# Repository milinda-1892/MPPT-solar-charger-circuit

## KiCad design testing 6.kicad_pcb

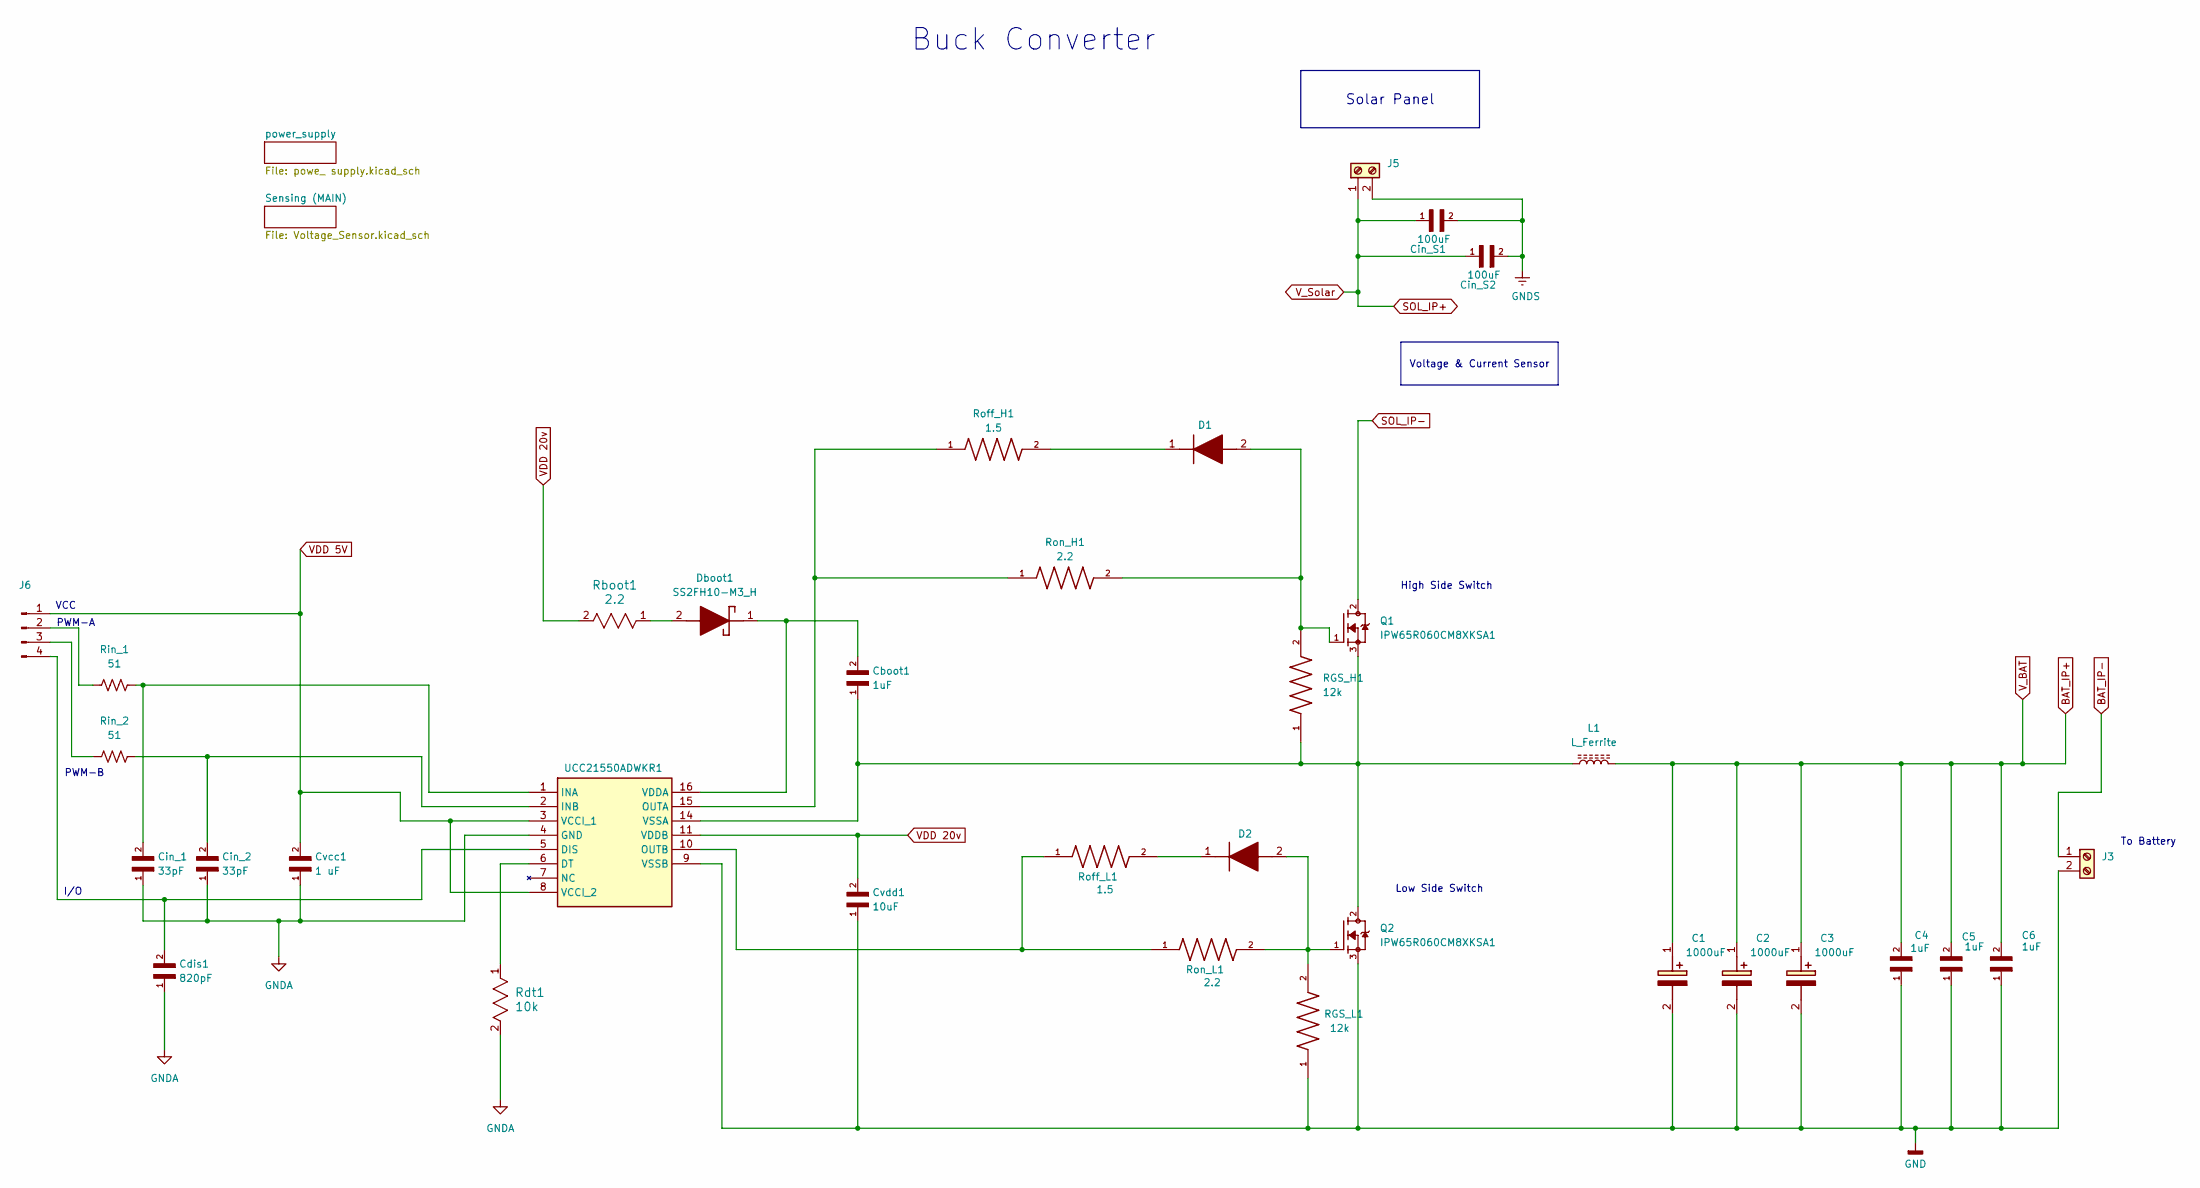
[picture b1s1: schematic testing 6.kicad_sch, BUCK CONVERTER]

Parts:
C1, C2, C3: 1000uF; CP_Radial_D16.0mm_P7.50mm; Mouser Part Number 594-MAL214699814E3
C4, C5, C6: 1uF; C_1210_3225Metric_Pad1.33x2.70mm_HandSolder
Cboot1: 1uF; C_1210_3225Metric_Pad1.33x2.70mm_HandSolder
Cdis1: 820pF; C_1206_3216Metric_Pad1.33x1.80mm_HandSolder
Cin_1, Cin_2: 33pF; C_0805_2012Metric_Pad1.18x1.45mm_HandSolder
Cin_S1, Cin_S2: 100uF; CP_Radial_D16.0mm_P7.50mm
Cvcc1: 1 uF; C_1210_3225Metric_Pad1.33x2.70mm_HandSolder
Cvdd1: 10uF; C_1210_3225Metric_Pad1.33x2.70mm_HandSolder
D1, D2: BYG20J-E3_TR; DIOM5127X229N; Mouser Part Number 625-BYG20J-E3
Dboot1: SS2FH10-M3_H; SODFL3718X108N; Mouser Part Number 78-SS2FH10-M3/H
J3, J5: Screw_Terminal_01x02; TerminalBlock_Phoenix_MPT-0,5-2-2.54_1x02_P2.54mm_Horizontal
J6: Conn_01x04_Pin; PinHeader_1x04_P2.00mm_Vertical
L1: L_Ferrite; L_Toroid_Vertical_L46.0mm_W19.1mm_P21.80mm_Bourns_5700
Q1, Q2: IPW65R060CM8XKSA1; TO544P521X1592X2557-3P; PARTREV 2.5
RGS_H1: 12k; R_1206_3216Metric_Pad1.30x1.75mm_HandSolder; PARTREV 3/1/2020
RGS_L1: 12k; R_1206_3216Metric_Pad1.30x1.75mm_HandSolder; PARTREV 3/1/2020
Rboot1: 2.2; R_0805_2012Metric_Pad1.20x1.40mm_HandSolder
Rdt1: 10k; R_0805_2012Metric_Pad1.20x1.40mm_HandSolder
Rin_1, Rin_2: 51; R_0805_2012Metric_Pad1.20x1.40mm_HandSolder
Roff_H1: 1.5; R_0805_2012Metric_Pad1.20x1.40mm_HandSolder
Roff_L1: 1.5; R_0805_2012Metric_Pad1.20x1.40mm_HandSolder
Ron_H1: 2.2; R_0805_2012Metric_Pad1.20x1.40mm_HandSolder
Ron_L1: 2.2; R_0805_2012Metric_Pad1.20x1.40mm_HandSolder
UCC21550ADWKR1: UCC21550ADWKR; UCC21550CDWKR; Mouser Part Number 595-UCC21550ADWKR

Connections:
BAT_IP+: C1.1 (+), C2.1 (+), C3.1 (+), C4.2, C5.2, C6.2, L1.2; also elsewhere on the board
BAT_IP-: J3.1; also elsewhere on the board
GND: C1.2 (-), C2.2 (-), C3.2 (-), C4.1, C5.1, C6.1, Cvdd1.1, J3.2, Q2.3, RGS_L1.1, UCC21550ADWKR1.9 (VSSB); also elsewhere on the board
GNDA: Cdis1.1, Cin_1.1, Cin_2.1, Cvcc1.1, Rdt1.2, UCC21550ADWKR1.4 (GND); also elsewhere on the board
GNDS: Cin_S1.2, Cin_S2.2, J5.2; also elsewhere on the board
unnamed: D1.2 (A), Q1.1, RGS_H1.2, Ron_H1.2
unnamed: D1.1 (K), Roff_H1.2
unnamed: D2.2 (A), Q2.1, RGS_L1.2, Ron_L1.2
unnamed: D2.1 (K), Roff_L1.2
unnamed: Dboot1.2 (A), Rboot1.1
unnamed: Cboot1.2, Dboot1.1 (K), UCC21550ADWKR1.16 (VDDA)
unnamed: J6.2, Rin_1.1
unnamed: J6.3, Rin_2.1
unnamed: Cdis1.2, J6.4, UCC21550ADWKR1.5 (DIS)
unnamed: Rdt1.1, UCC21550ADWKR1.6 (DT)
unnamed: Cin_1.2, Rin_1.2, UCC21550ADWKR1.1 (INA)
unnamed: Cin_2.2, Rin_2.2, UCC21550ADWKR1.2 (INB)
unnamed: Roff_H1.1, Ron_H1.1, UCC21550ADWKR1.15 (OUTA)
unnamed: Roff_L1.1, Ron_L1.1, UCC21550ADWKR1.10 (OUTB)
unnamed: Cboot1.1, L1.1, Q1.3, Q2.2, RGS_H1.1, UCC21550ADWKR1.14 (VSSA)
SOL_IP+: Cin_S1.1, Cin_S2.1, J5.1; also elsewhere on the board
SOL_IP-: Q1.2; also elsewhere on the board
VDD 5V: Cvcc1.2, J6.1, UCC21550ADWKR1.3 (VCCI_1), UCC21550ADWKR1.8 (VCCI_2); also elsewhere on the board
VDD 20v: Cvdd1.2, Rboot1.2, UCC21550ADWKR1.11 (VDDB); also elsewhere on the board

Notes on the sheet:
I/O
PWM-B
Low Side Switch
PWM-A
Buck Converter
High Side Switch
To Battery
VCC
Solar Panel
Voltage & Current Sensor

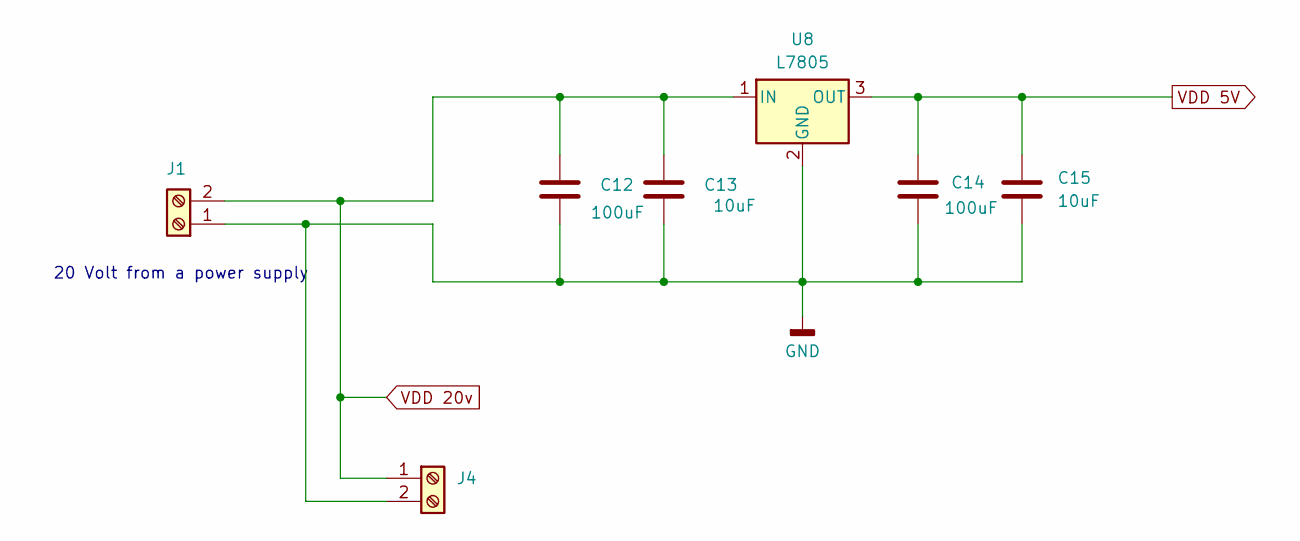
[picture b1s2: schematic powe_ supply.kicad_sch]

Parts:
C12, C14: 100uF; C_1206_3216Metric_Pad1.33x1.80mm_HandSolder
C13, C15: 10uF; C_1206_3216Metric_Pad1.33x1.80mm_HandSolder
J1, J4: Screw_Terminal_01x02; TerminalBlock_Phoenix_MPT-0,5-2-2.54_1x02_P2.54mm_Horizontal
U8: L7805; TO-252-3_TabPin2

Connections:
GND: C12.2, C13.2, C14.2, C15.2, J1.1, J4.2, U8.2 (GND); also elsewhere on the board
VDD 5V: C14.1, C15.1, U8.3 (OUT); also elsewhere on the board
VDD 20v: C12.1, C13.1, J1.2, J4.1, U8.1 (IN); also elsewhere on the board

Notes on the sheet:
20 Volt from a power supply

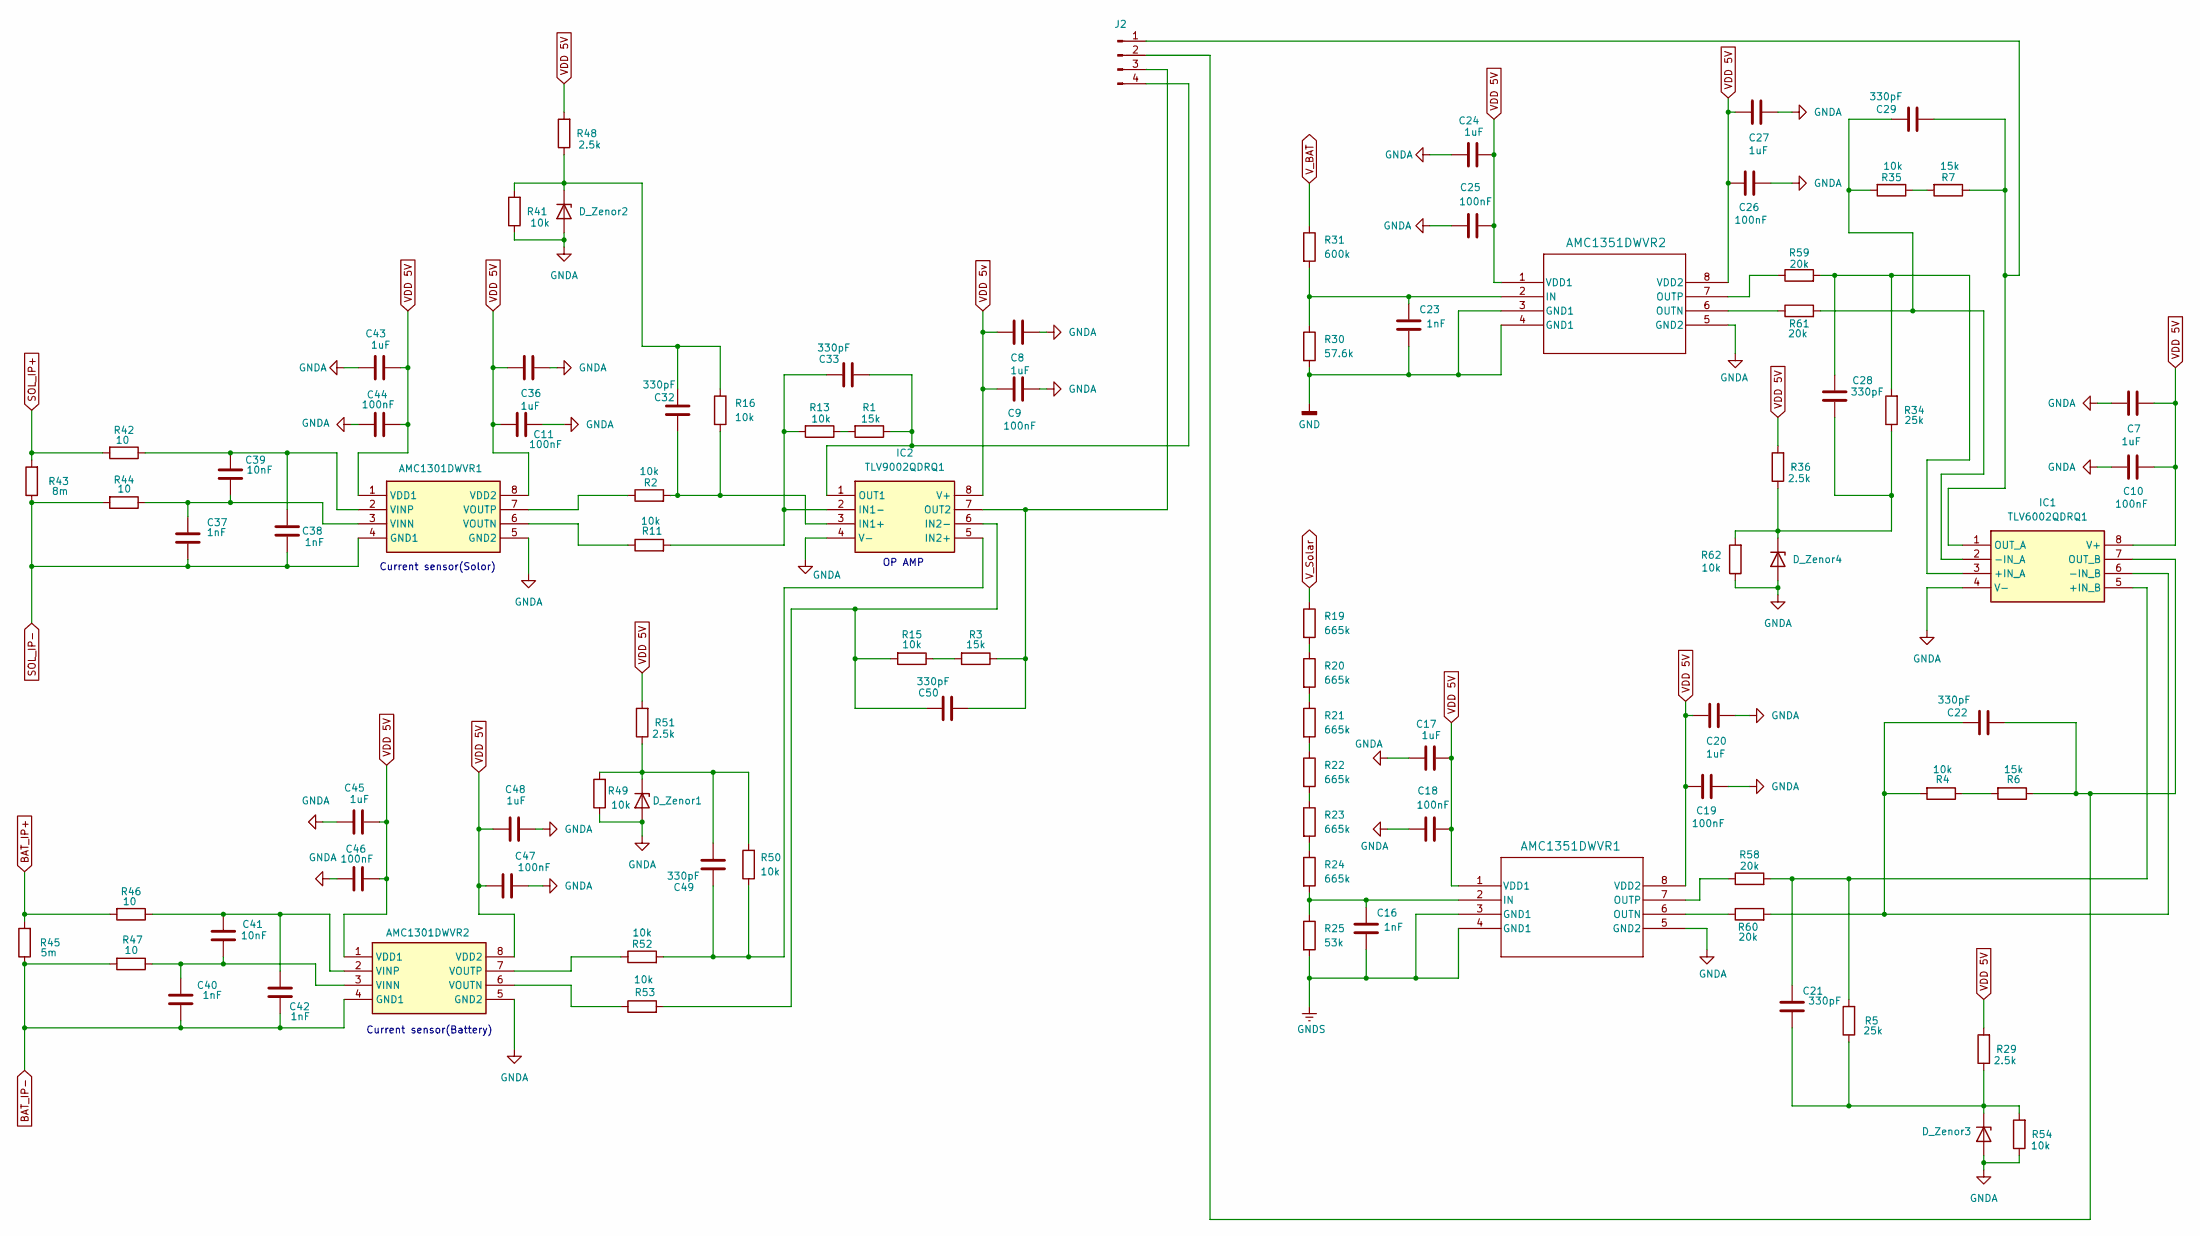
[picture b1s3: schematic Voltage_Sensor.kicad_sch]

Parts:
AMC1301DWVR1, AMC1301DWVR2: AMC1301DWVR; SOIC127P1150X280-8N; Mouser Part Number 595-AMC1301DWVR
AMC1351DWVR1, AMC1351DWVR2: AMC1351DWVR; SOIC127P1150X280-8N
C7, C8, C17, C20, C24, C27, C36, C43, C45, C48: 1uF; C_1206_3216Metric_Pad1.33x1.80mm_HandSolder
C9, C10, C11, C18, C19, C25, C26, C44, C46, C47: 100nF; C_1206_3216Metric_Pad1.33x1.80mm_HandSolder
C16, C23, C37, C38, C40, C42: 1nF; C_1206_3216Metric_Pad1.33x1.80mm_HandSolder
C21, C22, C28, C29, C32, C33, C49, C50: 330pF; C_1206_3216Metric_Pad1.33x1.80mm_HandSolder
C39, C41: 10nF; C_1206_3216Metric_Pad1.33x1.80mm_HandSolder
D_Zenor1, D_Zenor3: LM336; D_1206_3216Metric_Pad1.42x1.75mm_HandSolder
D_Zenor2: LM136-2; D_1206_3216Metric_Pad1.42x1.75mm_HandSolder
D_Zenor4: D_Zener; D_1206_3216Metric_Pad1.42x1.75mm_HandSolder
IC1: TLV6002QDRQ1; SOIC-8_3.9x4.9mm_P1.27mm; Mouser Part Number 595-TLV6002QDRQ1
IC2: TLV9002QDRQ1; SOIC-8_3.9x4.9mm_P1.27mm; Mouser Part Number 595-TLV9002QDRQ1
J2: Conn_01x04_Pin; PinHeader_1x04_P2.00mm_Vertical
R1, R3, R6, R7: 15k; R_1206_3216Metric_Pad1.30x1.75mm_HandSolder
R2, R4, R11, R13, R15, R16, R35, R41, R49, R50, R52, R53, R54, R62: 10k; R_1206_3216Metric_Pad1.30x1.75mm_HandSolder
R5, R34: 25k; R_1206_3216Metric_Pad1.30x1.75mm_HandSolder
R19, R20, R21, R22, R23, R24: 665k; R_1206_3216Metric_Pad1.30x1.75mm_HandSolder
R25: 53k; R_1206_3216Metric_Pad1.30x1.75mm_HandSolder
R29, R36, R48, R51: 2.5k; R_1206_3216Metric_Pad1.30x1.75mm_HandSolder
R30: 57.6k; R_1206_3216Metric_Pad1.30x1.75mm_HandSolder
R31: 600k; R_1206_3216Metric_Pad1.30x1.75mm_HandSolder
R42, R44, R46, R47: 10; R_1206_3216Metric_Pad1.30x1.75mm_HandSolder
R43: 8m; R_1206_3216Metric_Pad1.30x1.75mm_HandSolder
R45: 5m; R_1206_3216Metric_Pad1.30x1.75mm_HandSolder
R58, R59, R60, R61: 20k; R_1206_3216Metric_Pad1.30x1.75mm_HandSolder

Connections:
BAT_IP+: R31.1, R45.2, R46.2; also elsewhere on the board
BAT_IP-: AMC1301DWVR2.4 (GND1), C40.2, C42.2, R45.1, R47.2; also elsewhere on the board
GND: AMC1351DWVR2.3 (GND1), AMC1351DWVR2.4 (GND1), C23.2, R30.2; also elsewhere on the board
GNDA: AMC1301DWVR1.5 (GND2), AMC1301DWVR2.5 (GND2), AMC1351DWVR1.5 (GND2), AMC1351DWVR2.5 (GND2), C7.1, C8.1, C9.1, C10.1, C11.1, C17.1, C18.1, C19.1, C20.1, C24.1, C25.1, C26.1, C27.1, C36.1, C43.1, C44.1, C45.1, C46.1, C47.1, C48.1, D_Zenor1.2 (A), D_Zenor2.2 (A), D_Zenor3.2 (A), D_Zenor4.2 (A), IC1.4 (V-), IC2.4 (V-), R41.1, R49.1, R54.1, R62.1; also elsewhere on the board
GNDS: AMC1351DWVR1.3 (GND1), AMC1351DWVR1.4 (GND1), C16.2, R25.2; also elsewhere on the board
unnamed: AMC1301DWVR1.3 (VINN), C37.1, C39.2, R44.1
unnamed: AMC1301DWVR1.2 (VINP), C38.1, C39.1, R42.1
unnamed: AMC1301DWVR1.6 (VOUTN), R11.1
unnamed: AMC1301DWVR1.7 (VOUTP), R2.1
unnamed: AMC1301DWVR2.3 (VINN), C40.1, C41.2, R47.1
unnamed: AMC1301DWVR2.2 (VINP), C41.1, C42.1, R46.1
unnamed: AMC1301DWVR2.6 (VOUTN), R53.1
unnamed: AMC1301DWVR2.7 (VOUTP), R52.1
unnamed: AMC1351DWVR1.2 (IN), C16.1, R24.2, R25.1
unnamed: AMC1351DWVR1.6 (OUTN), R60.1
unnamed: AMC1351DWVR1.7 (OUTP), R58.1
unnamed: AMC1351DWVR2.2 (IN), C23.1, R30.1, R31.2
unnamed: AMC1351DWVR2.6 (OUTN), R61.1
unnamed: AMC1351DWVR2.7 (OUTP), R59.1
unnamed: C49.2, D_Zenor1.1 (K), R49.2, R50.2, R51.1
unnamed: C32.1, D_Zenor2.1 (K), R16.1, R41.2, R48.1
unnamed: C21.2, D_Zenor3.1 (K), R5.1, R29.1, R54.2
unnamed: C28.2, D_Zenor4.1 (K), R34.1, R36.1, R62.2
unnamed: C28.1, IC1.3 (+IN_A), R34.2, R59.2
unnamed: C21.1, IC1.5 (+IN_B), R5.2, R58.2
unnamed: C29.1, IC1.2 (-IN_A), R35.2, R61.2
unnamed: C22.1, IC1.6 (-IN_B), R4.2, R60.2
unnamed: C29.2, IC1.1 (OUT_A), J2.1, R7.1
unnamed: C22.2, IC1.7 (OUT_B), J2.2, R6.1
unnamed: C32.2, IC2.3 (IN1+), R2.2, R16.2
unnamed: C33.1, IC2.2 (IN1-), R11.2, R13.2
unnamed: C49.1, IC2.5 (IN2+), R50.1, R52.2
unnamed: C50.1, IC2.6 (IN2-), R15.2, R53.2
unnamed: C33.2, IC2.1 (OUT1), J2.4, R1.1
unnamed: C50.2, IC2.7 (OUT2), J2.3, R3.1
unnamed: R1.2, R13.1
unnamed: R4.1, R6.2
unnamed: R3.2, R15.1
unnamed: R19.2, R20.1
unnamed: R20.2, R21.1
unnamed: R21.2, R22.1
unnamed: R22.2, R23.1
unnamed: R23.2, R24.1
unnamed: R7.2, R35.1
SOL_IP+: R19.1, R42.2, R43.2; also elsewhere on the board
SOL_IP-: AMC1301DWVR1.4 (GND1), C37.2, C38.2, R43.1, R44.2; also elsewhere on the board
VDD 5V: AMC1301DWVR1.1 (VDD1), AMC1301DWVR1.8 (VDD2), AMC1301DWVR2.1 (VDD1), AMC1301DWVR2.8 (VDD2), AMC1351DWVR1.1 (VDD1), AMC1351DWVR1.8 (VDD2), AMC1351DWVR2.1 (VDD1), AMC1351DWVR2.8 (VDD2), C7.2, C10.2, C11.2, C17.2, C18.2, C19.2, C20.2, C24.2, C25.2, C26.2, C27.2, C36.2, C43.2, C44.2, C45.2, C46.2, C47.2, C48.2, IC1.8 (V+), R29.2, R36.2, R48.2, R51.2; also elsewhere on the board
VDD 5v: C8.2, C9.2, IC2.8 (V+)

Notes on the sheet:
Current sensor(Battery)
Current sensor(Solor)
OP AMP

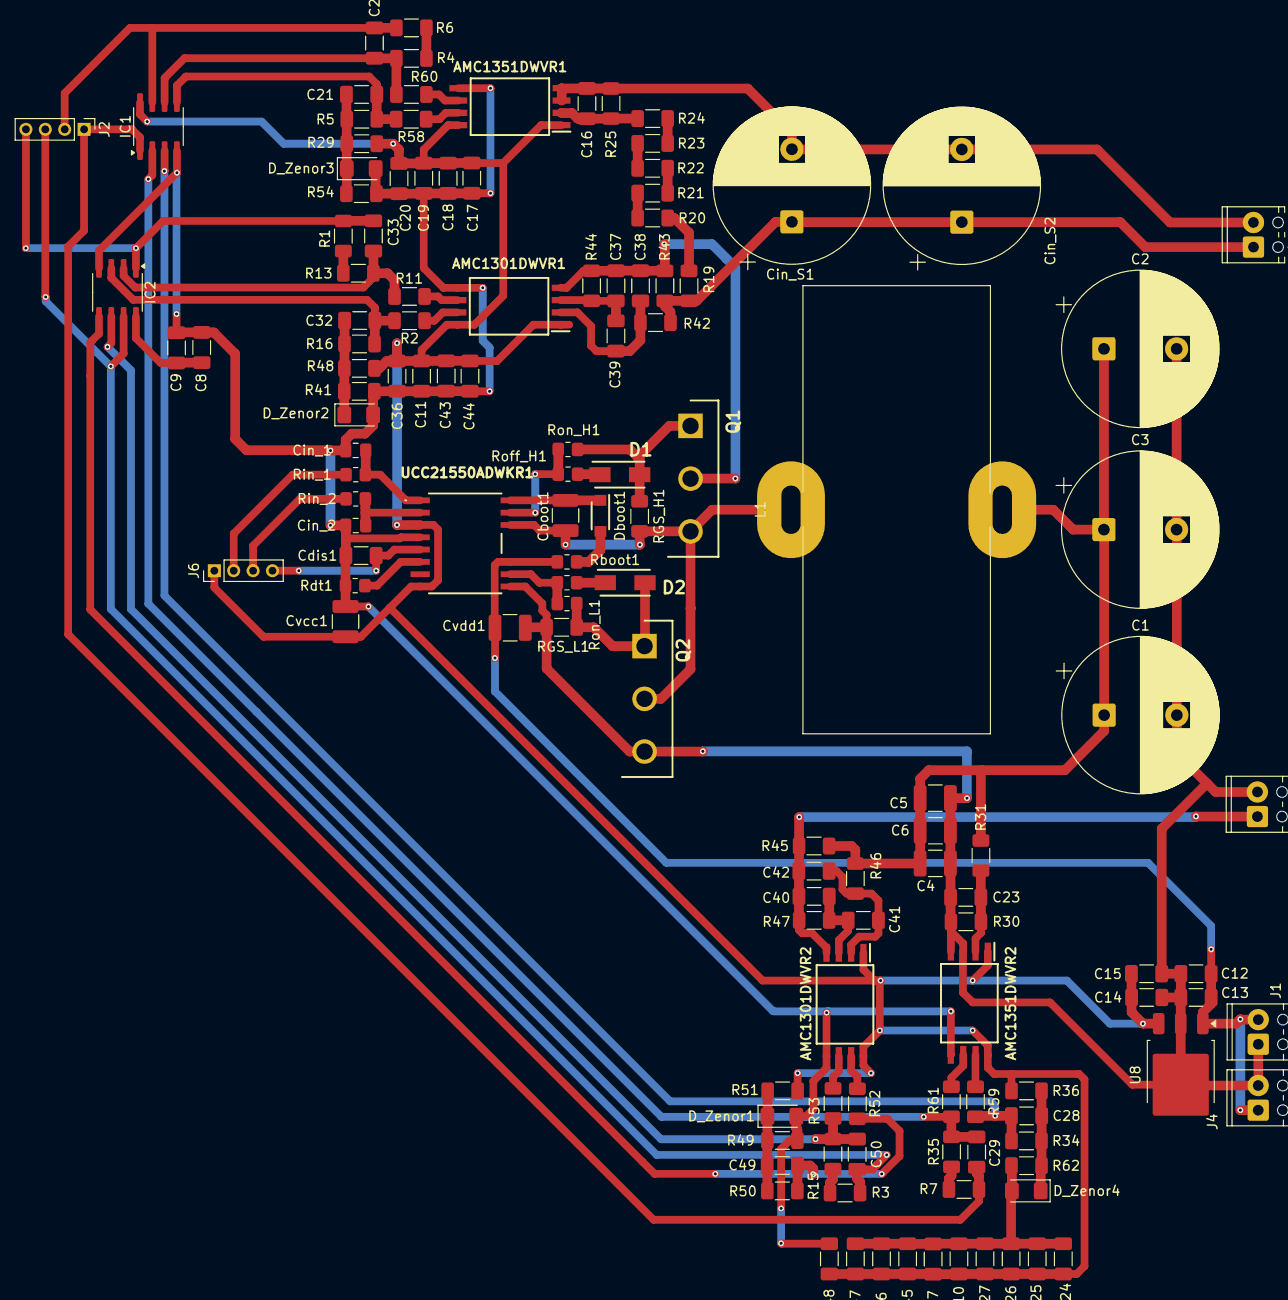
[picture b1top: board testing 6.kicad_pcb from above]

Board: 2 copper layers, 131 parts (0 on the bottom side), 64 nets.
